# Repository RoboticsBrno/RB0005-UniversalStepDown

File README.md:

# RB0005 – Universal Stepdown

[![I sell on
Tindie!](https://d2ss6ovg47m0r5.cloudfront.net/badges/tindie-mediums.png)](https://www.tindie.com/stores/yaqwsx/?ref=offsite_badges&utm_source=sellers_yaqwsx&utm_medium=badges&utm_campaign=badge_large)

Most of our projects at RoboticsBrno are powered either by Li-ion cells or 12V
power sources. However, most of our servos and boards require either 5V or 3V3
power source.

We used to buy cheap stepdown modules from Aliexpress to do the job. They are
inexpensive but their performance is questionable. Also, it is always a
surprise what you get in the envelope – some batches of them operate better,
some of them worse. One day, we decided to stop wasting our time with
poor-performing modules and we designed our own custom module – the RB0005
Universal Stepdown.

It is a simple and low-cost design based on the
[SY8105](https://file.remont-aud.net/baza/dc_dc/data/SY8105.pdf). And it gets
the job done – see the evaluation of our design below. You can also look at our
design on the [project
repository](https://github.com/RoboticsBrno/RB0005-UniversalStepDown).

## What does the module offer?

- there are two versions – 5V and 3.3V fixed output
- input voltage up to 18 V
- continuous load: 3 A (without cooling)/4 A (with cooling)
- pin compatible with 7805 linear voltage regulator and most of the Chinese modules
- has an enable pin (pull low to disable the module)
- small factor 10.5×19.5 mm
- low price: ~3 USD
- you know what to expect – we provide measurements of the module performance
    - **see the performance of [the 5V version](https://roboticsbrno.github.io/RB0005-UniversalStepDown/eval5v/index.html)**
    - **see the performance of [the 3V3 version](https://roboticsbrno.github.io/RB0005-UniversalStepDown/eval3v/index.html)**
    - **see the performance of [the 5V version v2](https://roboticsbrno.github.io/RB0005-UniversalStepDown/eval5v_v2)**

## What we do not provide?

- high-end, precision solution
    - we do not focus on incredibly high module efficiency
    - we do not focus on being low-noise

## FAQ

#### Why the "RB0005" prefix?

To quickly distinguish our projects at
[RoboticsBrno](https://github.com/RoboticsBrno/), e.g., when ordering, we
decided to give a each project a unique code.

#### Why is there no adjustable version?

We aim for usability. Usually, you need to lower your voltage to 5 V (servos) or
3.3 V (powering MCU) in DIY robotics. Having an adjustable version increases
the chances of misconfiguration.

#### Why should I use your module instead of $1 module from Aliexpress?

Well, it depends on your needs. If you need a certain level of reliability, it
might be beneficial to know what to expect from your device. With our stepdown,
you know it: see [evaluation of the 5V
version](https://roboticsbrno.github.io/RB0005-UniversalStepDown/eval5v/index.html)
or the [the 3V3
version](https://roboticsbrno.github.io/RB0005-UniversalStepDown/eval3v/index.html).
You could buy a module from Aliexpress and measure it by yourself. However, that
is laborious and you cannot be sure that you will get the same-performing module
when you order it again.

## Licence

[RB0005 – Universal
Stepdown](https://roboticsbrno.github.io/RB0005-UniversalStepDown/) by [Jan
Mrázek](https://honzamrazek.cz) is licensed under [CC BY-NC-SA
4.0 ](https://creativecommons.org/licenses/by-nc-sa/4.0).

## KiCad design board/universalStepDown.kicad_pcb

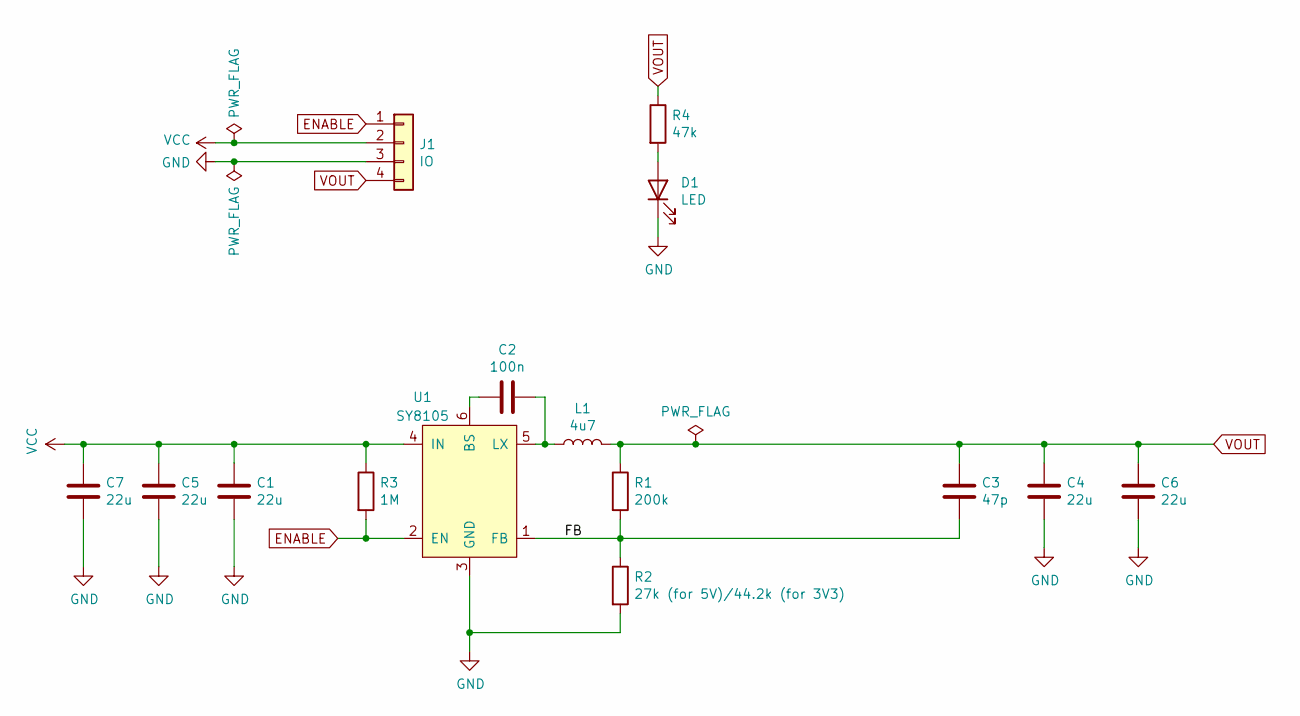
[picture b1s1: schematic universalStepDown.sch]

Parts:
C1, C4, C5, C6, C7: 22u; C_0805_2012Metric; LCSC C45783
C2: 100n; C_0603_1608Metric; LCSC C14663
C3: 47p; C_0402_1005Metric; LCSC C1567
D1: LED; LED_0603_1608Metric; LCSC C2286
J1: IO; PinHeader_1x04_P2.54mm_Horizontal
L1: 4u7; MWSA0503S; LCSC C408410
R1: 200k; R_0402_1005Metric; LCSC C25764
R2: 27k (for 5V)/44.2k (for 3V3); R_0402_1005Metric; LCSC_5V C25771
R3: 1M; R_0402_1005Metric; LCSC C26083
R4: 47k; R_0402_1005Metric; LCSC C25792
U1: SY8105; TSOT-23-6; LCSC C178247

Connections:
/FB: C3.1, R1.2, R2.1, U1.1 (FB)
ENABLE: J1.1, R3.2, U1.2 (EN)
GND: C1.2, C4.1, C5.2, C6.1, C7.2, D1.1 (K), J1.3, R2.2, U1.3 (GND)
unnamed: C2.1, L1.1, U1.5 (LX)
unnamed: C2.2, U1.6 (BS)
unnamed: D1.2 (A), R4.2
VCC: C1.1, C5.1, C7.1, J1.2, R3.1, U1.4 (IN)
VOUT: C3.2, C4.2, C6.2, J1.4, L1.2, R1.1, R4.1

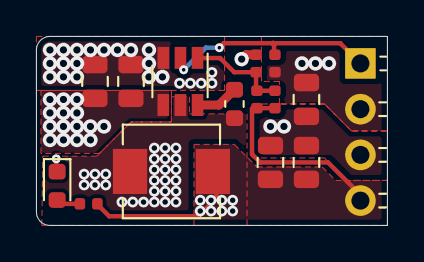
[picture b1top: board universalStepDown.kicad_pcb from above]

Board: 4 copper layers, 19.5 x 10.5 mm, 15 parts (0 on the bottom side), 8 nets.

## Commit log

2020-09-07 Add initial version
2020-09-13 Fix issues by cednik, prepare multi-voltage variant
2020-09-14 Prepare Makefile
2020-10-11 Prepare final fabrication data
2020-11-18 Prepare presentation
2020-11-19 Improve thermal design
2020-11-30 Fix typos
2020-12-07 Add link to Tindie
2020-12-15 Add evaluation of v0.2
2020-12-25 Add link to v2 evaluation
2020-12-25 Tweak label position
2021-01-05 Fix link to evaluation
2021-01-05 Fix typo in evaluation
2021-01-05 Deploy RoboticsBrno/RB0005-UniversalStepDown to github.com/RoboticsBrno/RB0005-UniversalStepDown.git:gh-pages
